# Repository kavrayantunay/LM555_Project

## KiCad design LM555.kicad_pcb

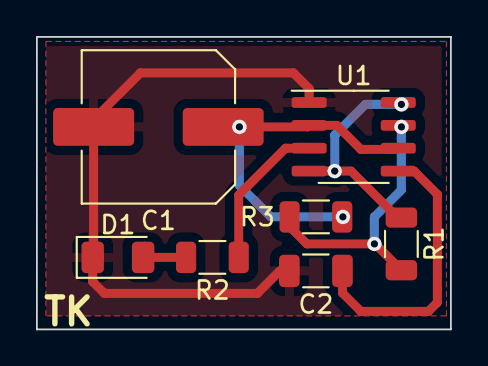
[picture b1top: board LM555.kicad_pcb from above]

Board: 2 copper layers, 23.0 x 16.2 mm, 7 parts (0 on the bottom side), 7 nets.

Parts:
C1: C; C_Elec_8x10.2
C2: C; C_1206_3216Metric
D1: LED; LED_1206_3216Metric
R1, R2, R3: R; R_1206_3216Metric
U1: LM555xM; SOIC-8_3.9x4.9mm_P1.27mm

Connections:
+9V: R1.1, U1.4 (R), U1.8 (VCC)
GND: C1.2, C2.2, D1.1 (K), U1.1 (GND)
unnamed: C1.1, R3.2, U1.2 (TR), U1.6 (THR)
unnamed: C2.1, U1.5 (CV)
unnamed: D1.2 (A), R2.2
unnamed: R1.2, R3.1, U1.7 (DIS)
unnamed: R2.1, U1.3 (Q)
